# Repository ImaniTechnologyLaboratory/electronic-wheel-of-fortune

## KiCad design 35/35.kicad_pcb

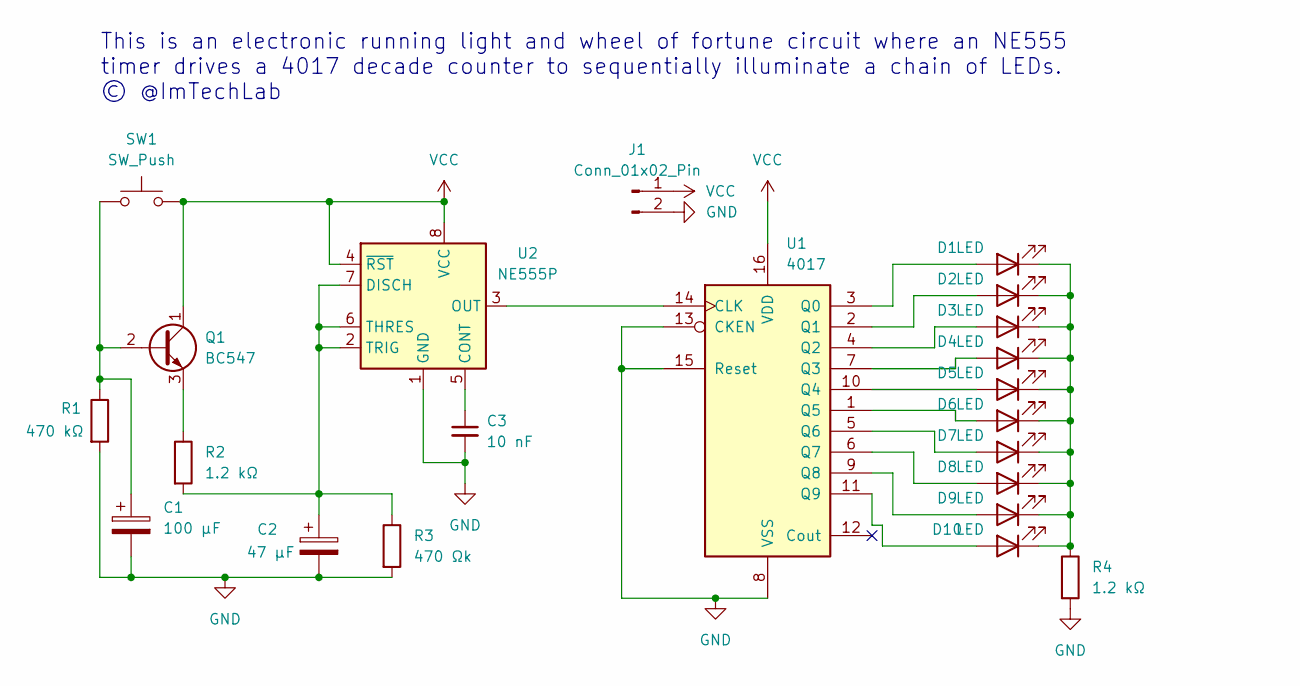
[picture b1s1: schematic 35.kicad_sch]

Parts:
C1: 100 µF; CP_Radial_D5.0mm_P2.00mm
C2: 47 µF; CP_Radial_D5.0mm_P2.00mm
C3: 10 nF; C_Disc_D3.8mm_W2.6mm_P2.50mm
D1, D2, D3, D4, D5, D6, D7, D8, D9, D10: LED; LED_D5.0mm
J1: Conn_01x02_Pin; PinHeader_1x02_P2.54mm_Vertical
Q1: BC547; TO-92_Inline
R1: 470 kΩ; R_Axial_DIN0207_L6.3mm_D2.5mm_P7.62mm_Horizontal
R2, R4: 1.2 kΩ; R_Axial_DIN0207_L6.3mm_D2.5mm_P7.62mm_Horizontal
R3: 470 Ωk; R_Axial_DIN0207_L6.3mm_D2.5mm_P7.62mm_Horizontal
SW1: SW_Push; SW_PUSH_6mm
U1: 4017; DIP-16_W7.62mm
U2: NE555P; DIP-8_W7.62mm

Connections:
GND: C1.2, C2.2, C3.2, J1.2, R1.2, R3.2, R4.2, U1.8 (VSS), U1.13 (CKEN), U1.15 (Reset), U2.1 (GND)
unnamed: D1.2 (A), U1.3 (Q0)
unnamed: D1.1 (K), D2.1 (K), D3.1 (K), D4.1 (K), D5.1 (K), D6.1 (K), D7.1 (K), D8.1 (K), D9.1 (K), D10.1 (K), R4.1
unnamed: D2.2 (A), U1.2 (Q1)
unnamed: D3.2 (A), U1.4 (Q2)
unnamed: D4.2 (A), U1.7 (Q3)
unnamed: D5.2 (A), U1.10 (Q4)
unnamed: D6.2 (A), U1.1 (Q5)
unnamed: D7.2 (A), U1.5 (Q6)
unnamed: D8.2 (A), U1.6 (Q7)
unnamed: D9.2 (A), U1.9 (Q8)
unnamed: D10.2 (A), U1.11 (Q9)
unnamed: C1.1, Q1.2 (B), R1.1, SW1.1
unnamed: Q1.3 (E), R2.1
unnamed: U1.14 (CLK), U2.3 (OUT)
unnamed: C3.1, U2.5 (CONT)
unnamed: C2.1, R2.2, R3.1, U2.2 (TRIG), U2.6 (THRES), U2.7 (DISCH)
VCC: J1.1, Q1.1 (C), SW1.2, U1.16 (VDD), U2.4 (~RST), U2.8 (VCC)

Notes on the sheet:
This is an electronic running light and wheel of fortune circuit where an NE555 timer drives a 4017 decade counter to sequentially illuminate a chain of LEDs. © @ImTechLab

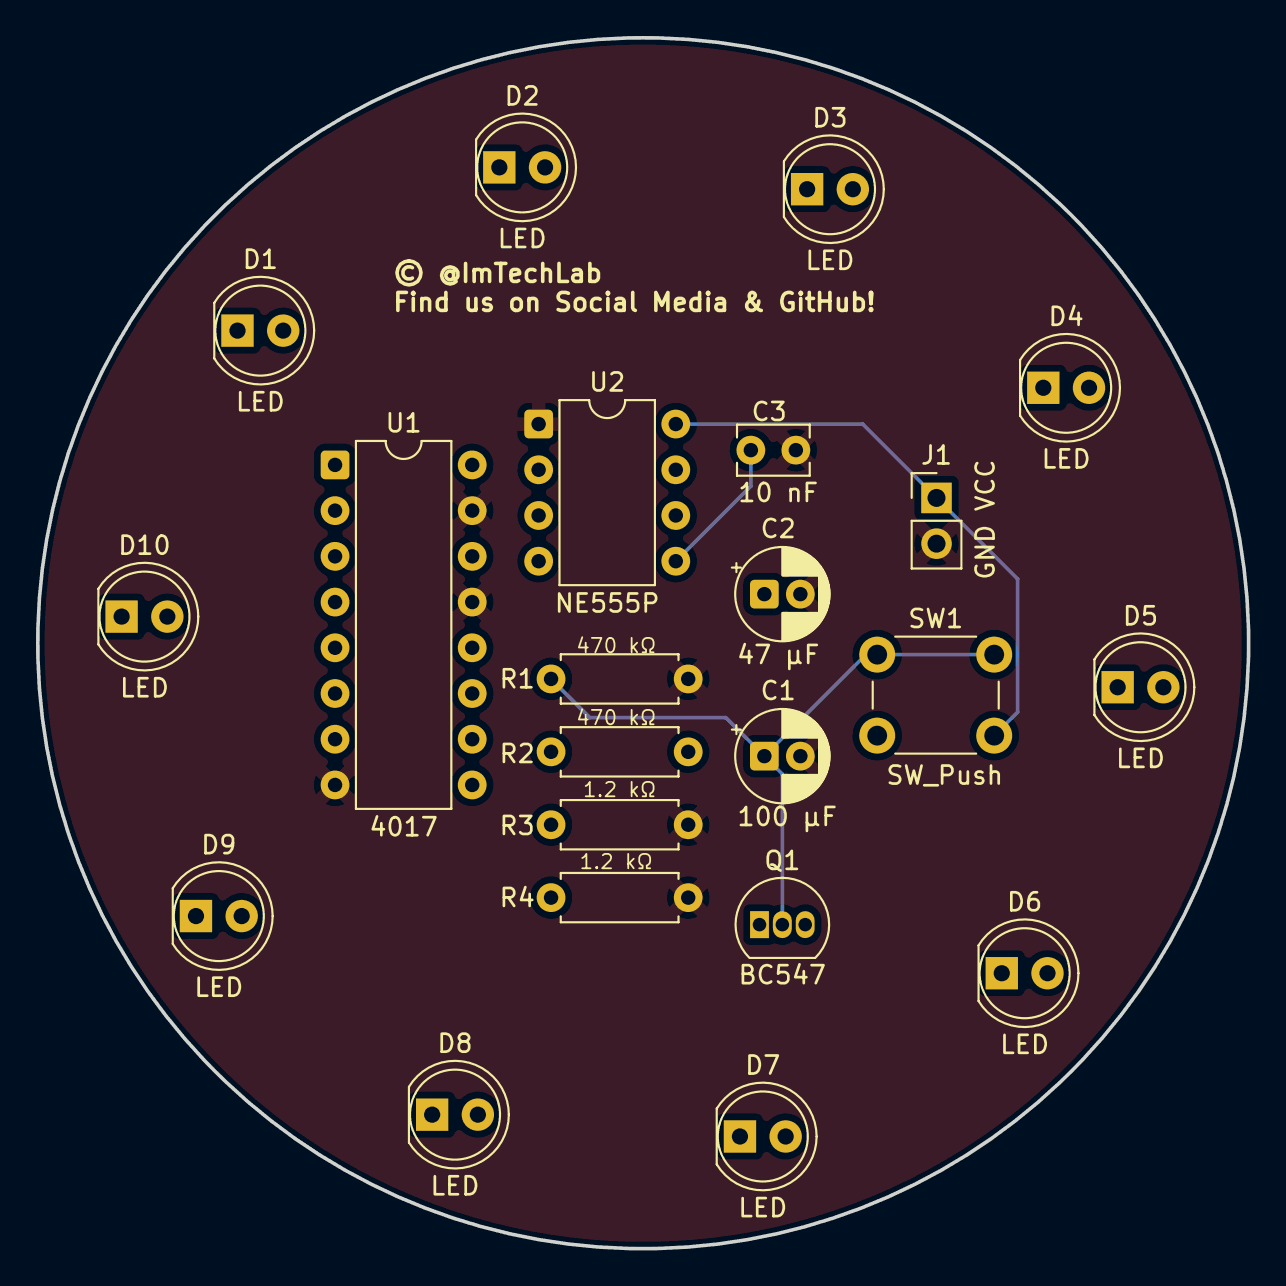
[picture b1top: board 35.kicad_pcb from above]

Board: 4 copper layers, 67.3 x 67.3 mm, 22 parts (0 on the bottom side), 18 nets.

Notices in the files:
35/35.kicad_pcb:
© 2026 All Rights Reserved
